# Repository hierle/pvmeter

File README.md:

# Energy meter - specifically for Solar Panels - for solarbildung.org
Current is sensed via transformer TA12-100 (100:1) and fed to ADC on an ESP32 board.
Sensor values are stored locally on LittleFS, and sent to cloud via Wifi and UMTS modem stick.

<br>
<br>

Contents:
- ./PCB/ :                  kicad PCB files
- ./cloud/ :                sample CGI script for data collection
- ./misc/ :                 images ...
- ./pvmeter/ :              pvmeter sketch (Arduino IDE)

Compiled and flashed with ArduinoIDE with ESP32 extensions

Features:
- using Lolin S2 mini based on ESP32S2
- transformer TA12-100 rated for 5A max, up to ~1kW
- real time clock DS3231 (I2C) ensures accurate timestamps for data logging
- TFT display via SPI can display status, current energy flow, ...
- USB UMTS modem stick provides reliable data upload even w/o Wifi avail
- USB command line interface for debugging and development

BOM (aliexpress):

| Count | Part number        | Description             | Usage                    |
|-------|--------------------|-------------------------|----------------------|
| 1     | Lolin-S2-miniNI    | CPU                     | CPU                  |
|       |                    |                         |                      |

S2 mini documentation:

https://www.wemos.cc/en/latest/s2/s2_mini.html

How to compile:

in short:<br>
- install ArduinoIDE from arduino.cc
- install the ESP32 Boards from Boards and Library Manager
- select "Lolin S2 mini" board
- on Mac you might need to install pyserial: sudo pip3 install pyserial
- on Linux you might need to install python3-pyserial
- connect the board
- select the corresponding serial port
- open the sketch folder
- adjust config.h and serialnr.h
- compile and flash

For configuration adjust config.h and serialnr.h

config.h:
- WIFI_SSID / WIFI_PASS: credentials for USB UMTS modem
- CLOUD_SERVER: server for data upload
- UPDATE_PERIOD: how often to update TFT display
- SENSOR_PERIOD: how often to measure and upload sensor data
- SENSOR_THRETHOLD: cut off noise below this value
- see also the comments for each entry in config.h

serialnr.h:
- SERIALNUMBER: serial number for specific device (who is sending the data?)

Additional notes:
- you will need a *DATA* USB-C cable, a charging only cable will not work, as it's missing the data pins ;-)

Todos:
- many :)

Have fun!

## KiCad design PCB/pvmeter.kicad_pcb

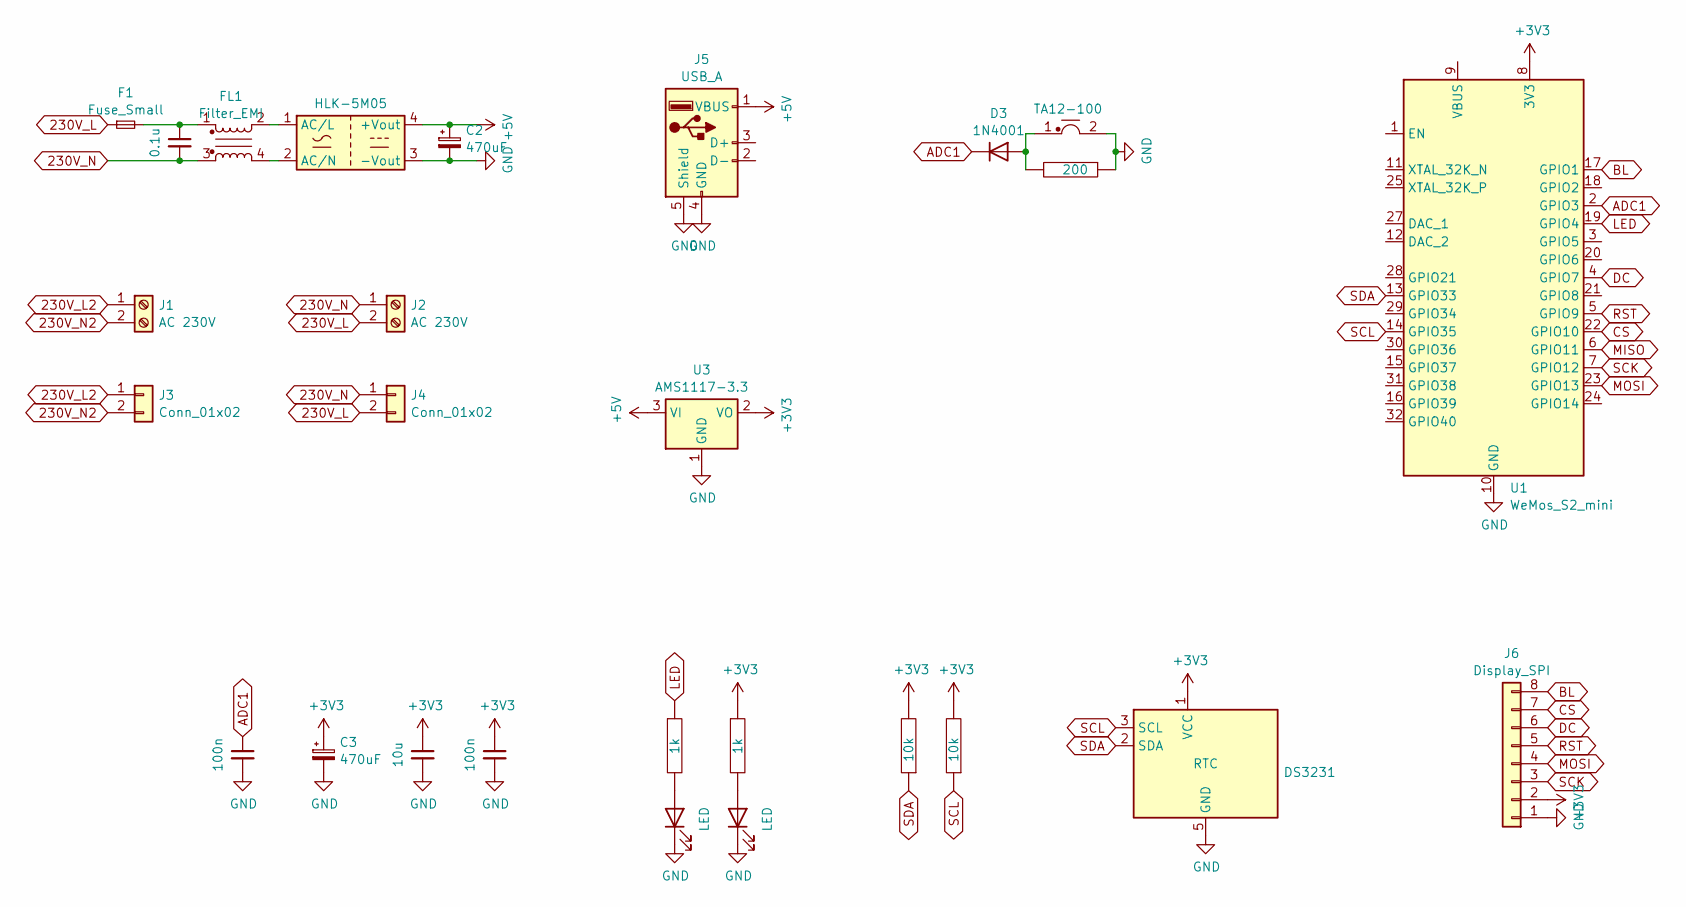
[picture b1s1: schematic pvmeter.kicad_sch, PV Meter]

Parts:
C1, C4: 100n; C_1206_3216Metric_Pad1.33x1.80mm_HandSolder
C2, C3: 470uF; CP_Radial_D8.0mm_P5.00mm
C5: 10u; C_1206_3216Metric_Pad1.33x1.80mm_HandSolder
C6: 0.1u; C_Rect_L11.0mm_W5.3mm_P10.00mm_MKT
D1, D2: LED; LED_PLCC_2835_Handsoldering
D3: 1N4001; Diode_1N4001_5x2.5mm_HandSolder
F1: Fuse_Small; Fuse_2512_6332Metric_Pad1.52x3.35mm_HandSolder
FL1: Filter_EMI; L_CommonMode_18x20mm_P10x13mm
J1, J2: AC 230V; Terminal_1x02_P7.62mm
J3, J4: Conn_01x02; Solder-Terminal_1x02_P7.62
J5: USB_A; USB_A_Molex_67643_Horizontal
J6: Display_SPI; PinHeader_1x08_P2.54mm_Vertical
PS1: HLK-5M05; HLK-5MXX
R1, R2: 1k; R_1206_3216Metric
R3, R4: 10k; R_1206_3216Metric
R5: 200; R_1206_3216Metric
TR1: TA12-100; Transformer_TA12-100
U1: WeMos_S2_mini; WEMOS-S2-mini
U2: DS3231; RTC_DS3231
U3: AMS1117-3.3; SOT-223

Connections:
230V_L: F1.1, J2.2, J4.2
230V_L2: J1.1, J3.1
230V_N: C6.2, FL1.3, J2.1, J4.1
230V_N2: J1.2, J3.2
+3V3: C3.1, C4.1, C5.1, J6.2, R1.1, R3.2, R4.2, U1.8 (3V3), U2.1 (VCC), U3.2 (VO)
+5V: C2.1, J5.1 (VBUS), PS1.4 (+Vout), U3.3 (VI)
ADC1: C1.1, D3.1 (K), U1.2 (GPIO3)
BL: J6.8, U1.17 (GPIO1)
CS: J6.7, U1.22 (GPIO10)
DC: J6.6, U1.4 (GPIO7)
GND: C1.2, C2.2, C3.2, C4.2, C5.2, D1.1 (K), D2.1 (K), J5.4 (GND), J5.5 (Shield), J6.1, PS1.3 (-Vout), R5.1, TR1.2, U1.10 (GND), U1.26 (GND), U2.5 (GND), U3.1 (GND)
LED: R2.1, U1.19 (GPIO4)
MISO: U1.6 (GPIO11)
MOSI: J6.4, U1.23 (GPIO13)
unnamed: C6.1, F1.2, FL1.1
unnamed: D1.2 (A), R1.2
unnamed: D2.2 (A), R2.2
unnamed: D3.2 (A), R5.2, TR1.1
unnamed: FL1.2, PS1.1 (AC/L)
unnamed: FL1.4, PS1.2 (AC/N)
RST: J6.5, U1.5 (GPIO9)
SCK: J6.3, U1.7 (GPIO12)
SCL: R4.1, U1.14 (GPIO35), U2.3 (SCL)
SDA: R3.1, U1.13 (GPIO33), U2.2 (SDA)

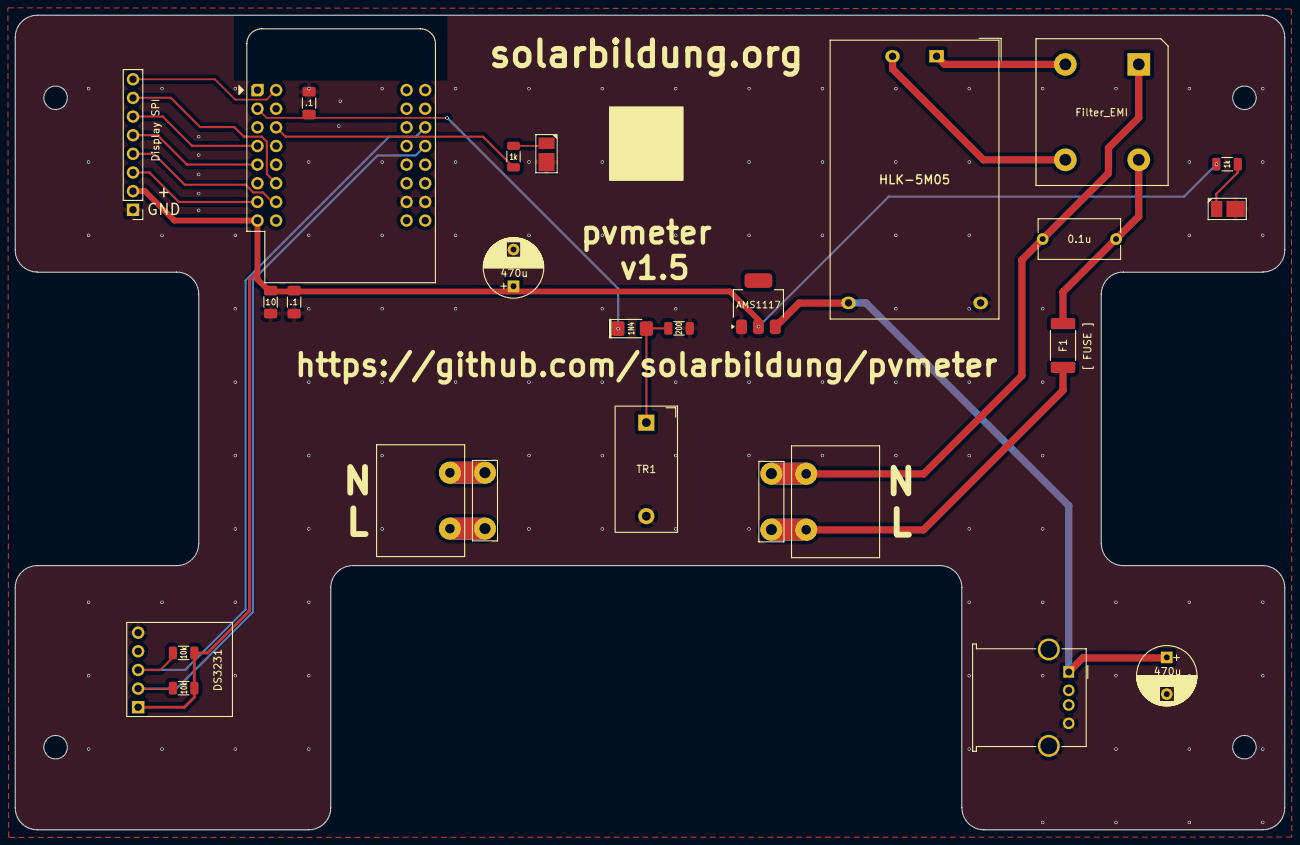
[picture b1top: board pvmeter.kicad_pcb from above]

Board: 2 copper layers, 173.0 x 111.0 mm, 27 parts (0 on the bottom side), 23 nets.

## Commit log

2025-12-11 apache config patch for ScriptAlias
